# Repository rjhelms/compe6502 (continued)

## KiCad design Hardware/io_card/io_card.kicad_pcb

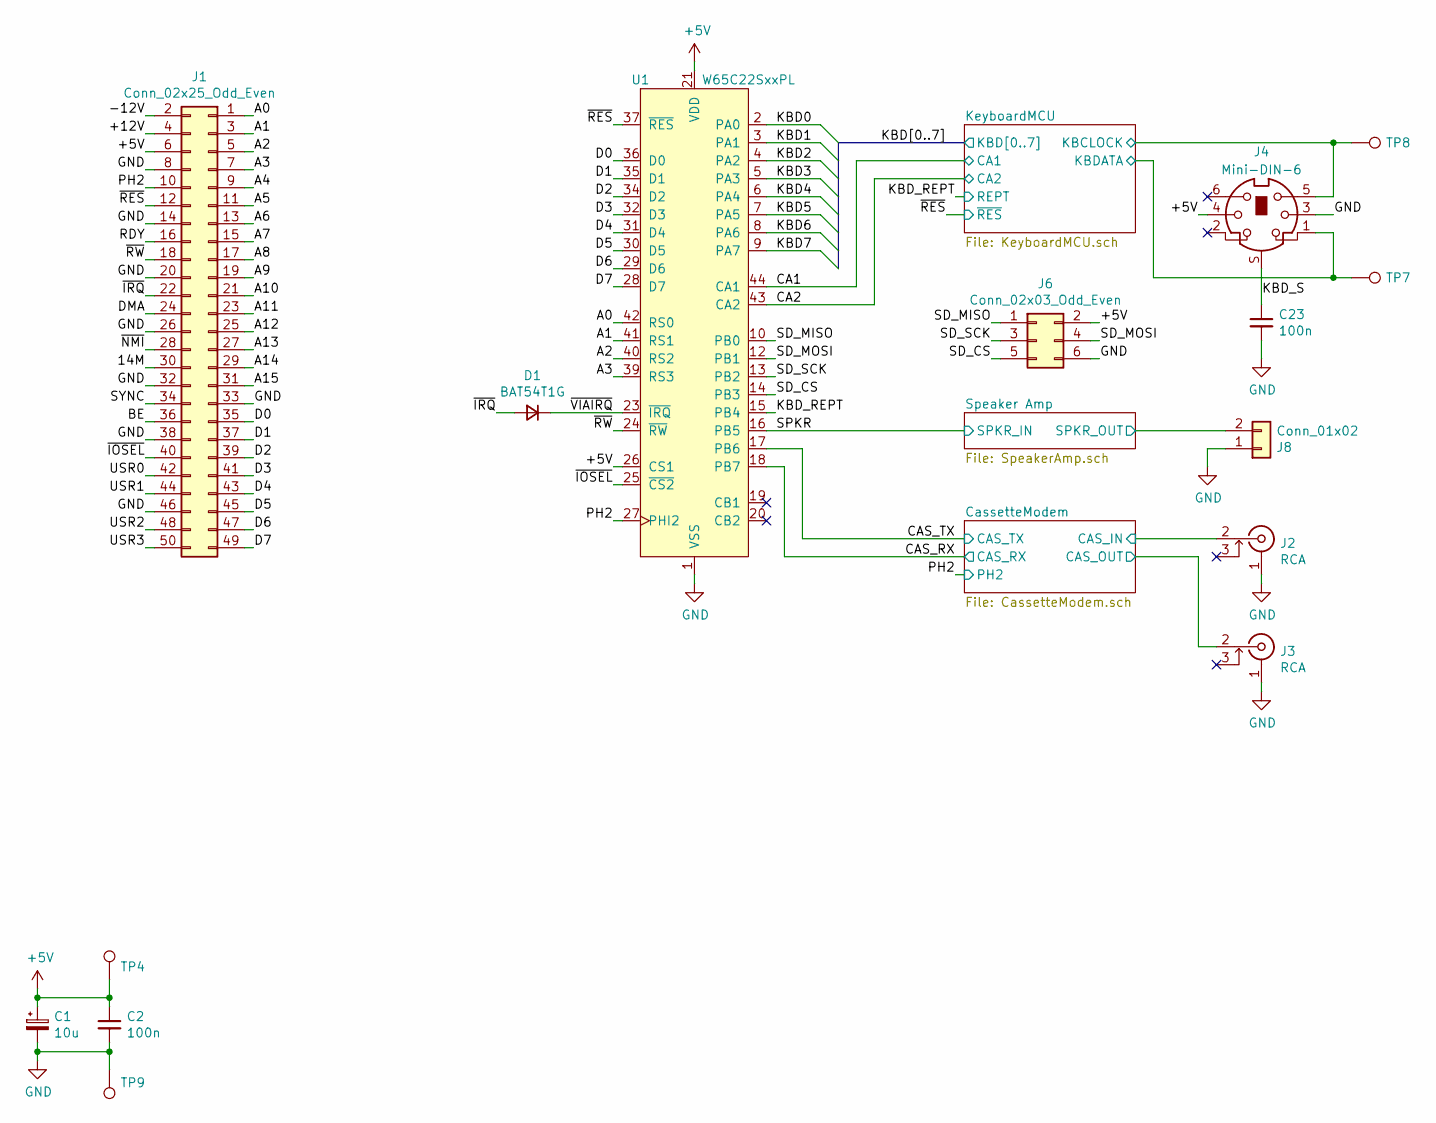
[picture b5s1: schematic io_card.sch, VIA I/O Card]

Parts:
C1: 10u; C_0805_2012Metric; MPN GRM21BR61E106KA73L
C2, C23: 100n; C_0805_2012Metric; MPN 08055C104JAT2A
D1: BAT54T1G; D_SOD-123; MPN BAT54T1G
J1: Conn_02x25_Odd_Even; EDAC_345-050-520-202_CardEdge; MPN 345-050-520-202
J2, J3: RCA; Jack_RCA_Switchcraft_PJRAN1X1UxxX; MPN PJRAN1X1U02AUX
J4: Mini-DIN-6; CUI_MD-60S; MPN MD-60S
J6: Conn_02x03_Odd_Even; IDC-Header_2x03_P2.54mm_Vertical; MPN 54020-44030LF
J8: Conn_01x02; PinHeader_1x02_P2.54mm_Horizontal
TP4, TP7, TP8, TP9: TestPoint; TestPoint_Keystone_5015_Micro-Minature; MPN S1751-46R
U1: W65C22SxxPL; PLCC-44_THT-Socket; MPN W65C22S6TPLG-14

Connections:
+5V: C1.1, C2.1, J1.6, J4.4, J6.2, TP4.1, U1.21 (VDD), U1.26 (CS1); also elsewhere on the board
/14M: J1.30
/+12V: J1.4
/-12V: J1.2
/A0: J1.1, U1.42 (RS0)
/A1: J1.3, U1.41 (RS1)
/A2: J1.5, U1.40 (RS2)
/A3: J1.7, U1.39 (RS3)
/A4: J1.9
/A5: J1.11
/A6: J1.13
/A7: J1.15
/A8: J1.17
/A9: J1.19
/A10: J1.21
/A11: J1.23
/A12: J1.25
/A13: J1.27
/A14: J1.29
/A15: J1.31
/BE: J1.36
/CA1: U1.44 (CA1); also elsewhere on the board
/CA2: U1.43 (CA2); also elsewhere on the board
/CAS_RX: U1.18 (PB7); also elsewhere on the board
/CAS_TX: U1.17 (PB6); also elsewhere on the board
/CassetteModem/CAS_IN: J2.2 (In); also elsewhere on the board
/CassetteModem/CAS_OUT: J3.2 (In); also elsewhere on the board
/D0: J1.35, U1.36 (D0)
/D1: J1.37, U1.35 (D1)
/D2: J1.39, U1.34 (D2)
/D3: J1.41, U1.32 (D3)
/D4: J1.43, U1.31 (D4)
/D5: J1.45, U1.30 (D5)
/D6: J1.47, U1.29 (D6)
/D7: J1.49, U1.28 (D7)
/DMA: J1.24
/KBD0: U1.2 (PA0); also elsewhere on the board
/KBD1: U1.3 (PA1); also elsewhere on the board
/KBD2: U1.4 (PA2); also elsewhere on the board
/KBD3: U1.5 (PA3); also elsewhere on the board
/KBD4: U1.6 (PA4); also elsewhere on the board
/KBD5: U1.7 (PA5); also elsewhere on the board
/KBD6: U1.8 (PA6); also elsewhere on the board
/KBD7: U1.9 (PA7); also elsewhere on the board
/KBD_REPT: U1.15 (PB4); also elsewhere on the board
/KBD_S: C23.1, J4.S
/KeyboardMCU/KBCLOCK: J4.5, TP8.1; also elsewhere on the board
/KeyboardMCU/KBDATA: J4.1, TP7.1; also elsewhere on the board
/PH2: J1.10, U1.27 (PHI2); also elsewhere on the board
/RDY: J1.16
/SD_CS: J6.5, U1.14 (PB3)
/SD_MISO: J6.1, U1.10 (PB0)
/SD_MOSI: J6.4, U1.12 (PB1)
/SD_SCK: J6.3, U1.13 (PB2)
/SPKR: U1.16 (PB5); also elsewhere on the board
/SYNC: J1.34
/Speaker Amp/SPKR_OUT: J8.2; also elsewhere on the board
/USR0: J1.42
/USR1: J1.44
/USR2: J1.48
/USR3: J1.50
/~IOSEL: J1.40, U1.25 (~CS2)
/~IRQ: D1.2 (A), J1.22
/~NMI: J1.28
/~RES: J1.12, U1.37 (~RES); also elsewhere on the board
/~RW: J1.18, U1.24 (~RW)
/~VIAIRQ: D1.1 (K), U1.23 (~IRQ)
GND: C1.2, C2.2, C23.2, J1.8, J1.14, J1.20, J1.26, J1.32, J1.33, J1.38, J1.46, J2.1 (Ext), J3.1 (Ext), J4.3, J6.6, J8.1, TP9.1, U1.1 (VSS); also elsewhere on the board

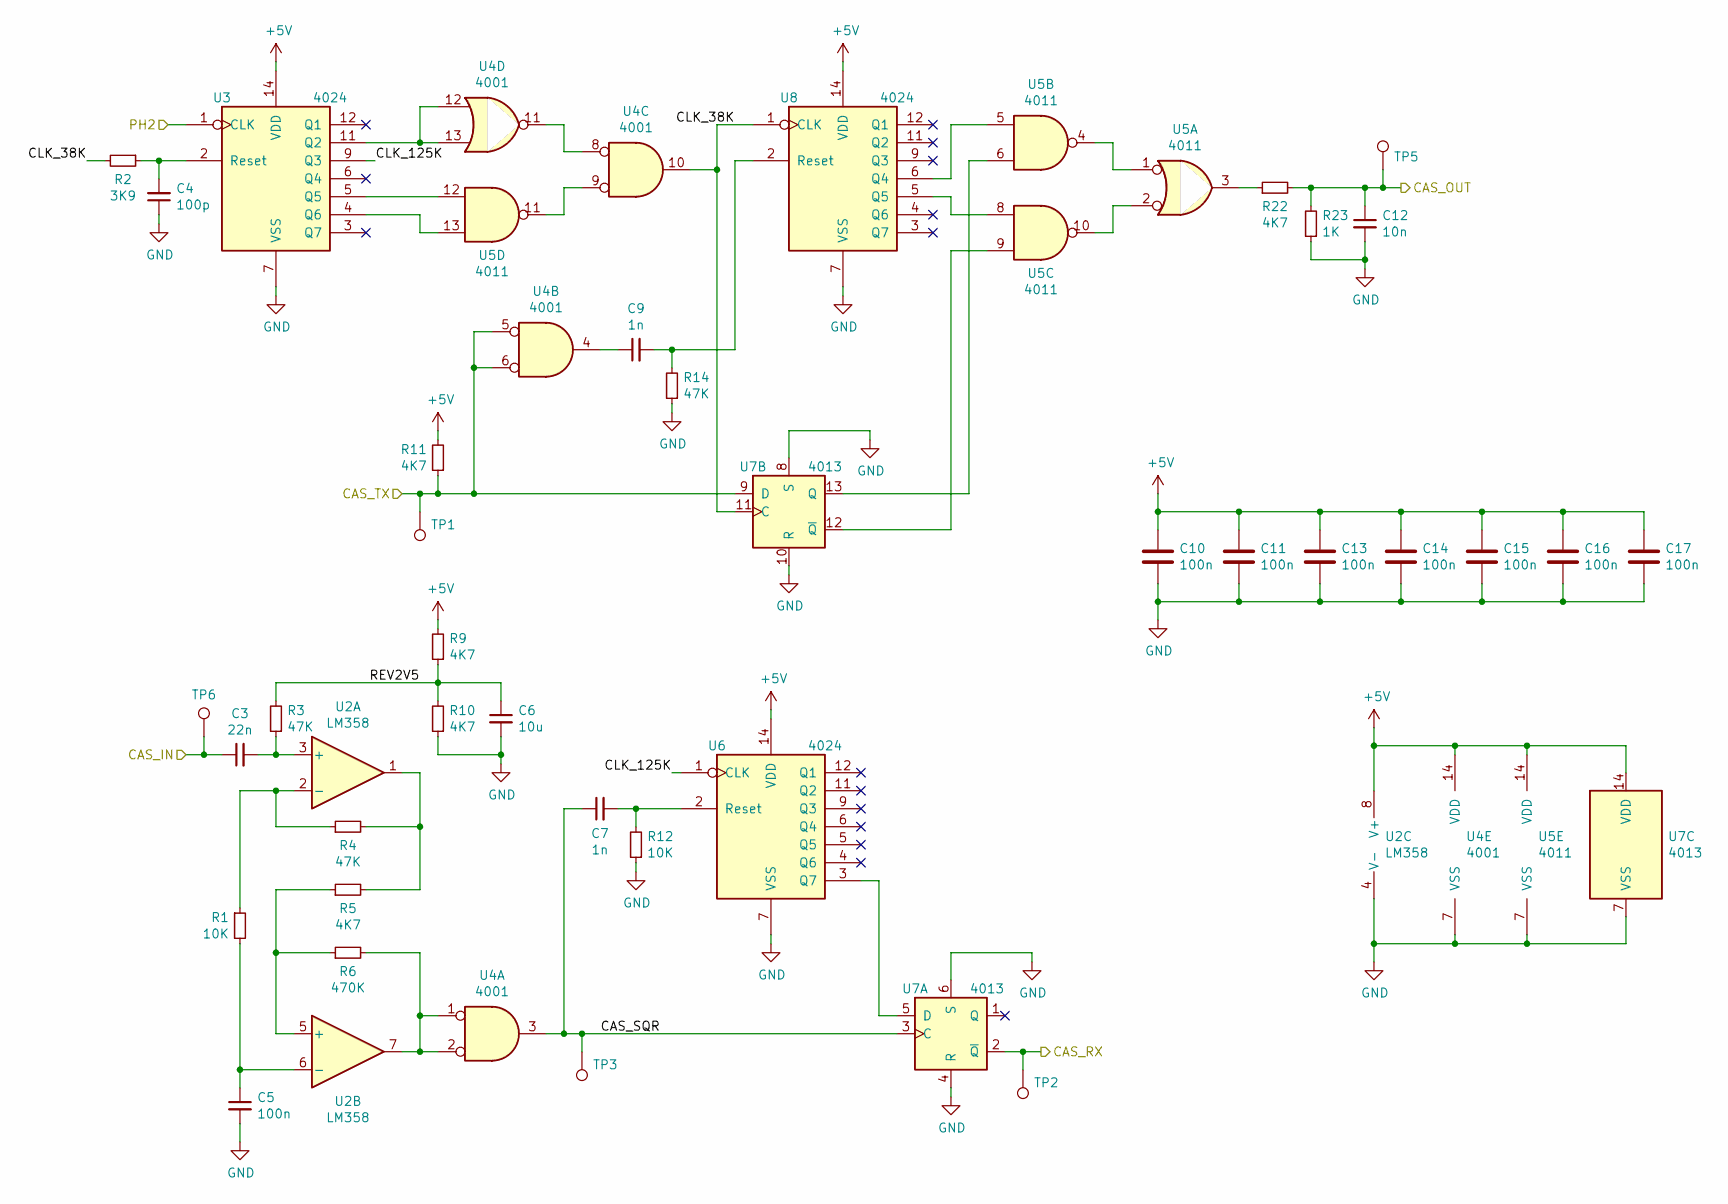
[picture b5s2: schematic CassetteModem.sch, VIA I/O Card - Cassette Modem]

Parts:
C3: 22n; C_0805_2012Metric; MPN CL21B223KBANNWC
C4: 100p; C_0805_2012Metric; MPN 885012007034
C5, C10, C11, C13, C14, C15, C16, C17: 100n; C_0805_2012Metric; MPN 08055C104JAT2A
C6: 10u; C_0805_2012Metric; MPN GRM21BR61E106KA73L
C7, C9: 1n; C_0805_2012Metric; MPN CL21B102KBANNND
C12: 10n; C_0805_2012Metric; MPN CL21B103KBANFNC
R1, R12: 10K; R_0805_2012Metric; MPN MCSR08X1002FTL
R2: 3K9; R_0805_2012Metric; MPN CR0805-FX-3901ELF
R3, R4, R14: 47K; R_0805_2012Metric; MPN RC0805FR-0747KL
R5, R9, R10, R11, R22: 4K7; R_0805_2012Metric; MPN CRCW08054K70FKTA
R6: 470K; R_0805_2012Metric; MPN RC0805FR-07470KL
R23: 1K; R_0805_2012Metric; MPN CRCW08051K00FKEB
TP1, TP2, TP3, TP5, TP6: TestPoint; TestPoint_Keystone_5015_Micro-Minature; MPN S1751-46R
U2: LM358; SOIC-8_3.9x4.9mm_P1.27mm; MPN LM358PSR
U3, U6, U8: 4024; SOIC-14_3.9x8.7mm_P1.27mm; MPN CD4024BM96
U4: 4001; SOIC-14_3.9x8.7mm_P1.27mm; MPN HEF4001BT-Q100J
U5: 4011; SOIC-14_3.9x8.7mm_P1.27mm; MPN MC14011BDR2G
U7: 4013; SOIC-14_3.9x8.7mm_P1.27mm; MPN HEF4013BT,653

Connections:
+5V: C10.1, C11.1, C13.1, C14.1, C15.1, C16.1, C17.1, R9.2, R11.2, U2.8 (V+), U3.14 (VDD), U4.14 (VDD), U5.14 (VDD), U6.14 (VDD), U7.14 (VDD), U8.14 (VDD); also elsewhere on the board
/CAS_RX: TP2.1, U7.2 (~Q); also elsewhere on the board
/CAS_TX: R11.1, TP1.1, U4.5, U4.6, U7.9 (D); also elsewhere on the board
/CassetteModem/CAS_IN: C3.1, TP6.1; also elsewhere on the board
/CassetteModem/CAS_OUT: C12.1, R22.2, R23.2, TP5.1; also elsewhere on the board
/CassetteModem/CAS_SQR: C7.1, TP3.1, U4.3, U7.3 (C)
/CassetteModem/CLK_38K: R2.2, U4.10, U7.11 (C), U8.1 (CLK)
/CassetteModem/CLK_125K: U3.9 (Q3), U6.1 (CLK)
/CassetteModem/REV2V5: C6.1, R3.2, R9.1, R10.2
/PH2: U3.1 (CLK); also elsewhere on the board
GND: C4.1, C5.2, C6.2, C10.2, C11.2, C12.2, C13.2, C14.2, C15.2, C16.2, C17.2, R10.1, R12.1, R14.1, R23.1, U2.4 (V-), U3.7 (VSS), U4.7 (VSS), U5.7 (VSS), U6.7 (VSS), U7.4 (R), U7.6 (S), U7.7 (VSS), U7.8 (S), U7.10 (R), U8.7 (VSS); also elsewhere on the board
unnamed: C3.2, R3.1, U2.3 (+)
unnamed: C4.2, R2.1, U3.2 (Reset)
unnamed: C5.1, R1.2, U2.6 (-)
unnamed: C7.2, R12.2, U6.2 (Reset)
unnamed: C9.1, U4.4
unnamed: C9.2, R14.2, U8.2 (Reset)
unnamed: R1.1, R4.1, U2.2 (-)
unnamed: R4.2, R5.2, U2.1
unnamed: R5.1, R6.1, U2.5 (+)
unnamed: R6.2, U2.7, U4.1, U4.2
unnamed: R22.1, U5.3
unnamed: U3.4 (Q6), U5.13
unnamed: U3.5 (Q5), U5.12
unnamed: U3.11 (Q2), U4.12, U4.13
unnamed: U4.9, U5.11
unnamed: U4.8, U4.11
unnamed: U5.1, U5.4
unnamed: U5.5, U8.6 (Q4)
unnamed: U5.6, U7.13 (Q)
unnamed: U5.8, U8.5 (Q5)
unnamed: U5.9, U7.12 (~Q)
unnamed: U5.2, U5.10
unnamed: U6.3 (Q7), U7.5 (D)

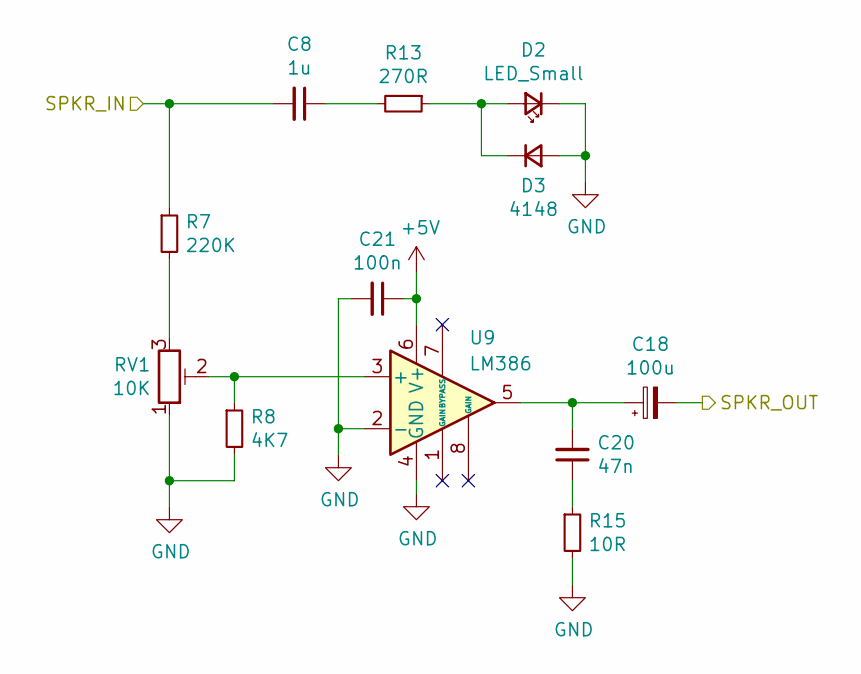
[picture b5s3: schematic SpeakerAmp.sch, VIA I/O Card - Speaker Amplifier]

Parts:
C8: 1u; C_0805_2012Metric; MPN 08053C105K4Z4A
C18: 100u; CP_Elec_6.3x5.4; MPN 865080343009
C20: 47n; C_0805_2012Metric; MPN CL21B473KBCNNNC
C21: 100n; C_0805_2012Metric; MPN 08055C104JAT2A
D2: LED_Small; LED_0805_2012Metric; MPN 598-8170-107F
D3: 4148; D_SOD-123; MPN MMSD4148T1G
R7: 220K; R_0805_2012Metric; MPN RC0805FR-07220KL
R8: 4K7; R_0805_2012Metric; MPN CRCW08054K70FKTA
R13: 270R; R_0805_2012Metric; MPN RC0805FR-07270RL
R15: 10R; R_0805_2012Metric; MPN CR0805-FX-10R0ELF
RV1: 10K; Potentiometer_Copal_CT-6EP; MPN CT6EP103
U9: LM386; SOIC-8_3.9x4.9mm_P1.27mm; MPN LM386M-1/NOPB

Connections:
+5V: C21.1, U9.6 (V+); also elsewhere on the board
/SPKR: C8.2, R7.1; also elsewhere on the board
/Speaker Amp/SPKR_OUT: C18.2; also elsewhere on the board
GND: C21.2, D2.1 (K), D3.2 (A), R8.2, R15.2, RV1.1, U9.2 (-), U9.4 (GND); also elsewhere on the board
unnamed: C8.1, R13.2
unnamed: C18.1, C20.2, U9.5
unnamed: C20.1, R15.1
unnamed: D2.2 (A), D3.1 (K), R13.1
unnamed: R7.2, RV1.3
unnamed: R8.1, RV1.2, U9.3 (+)

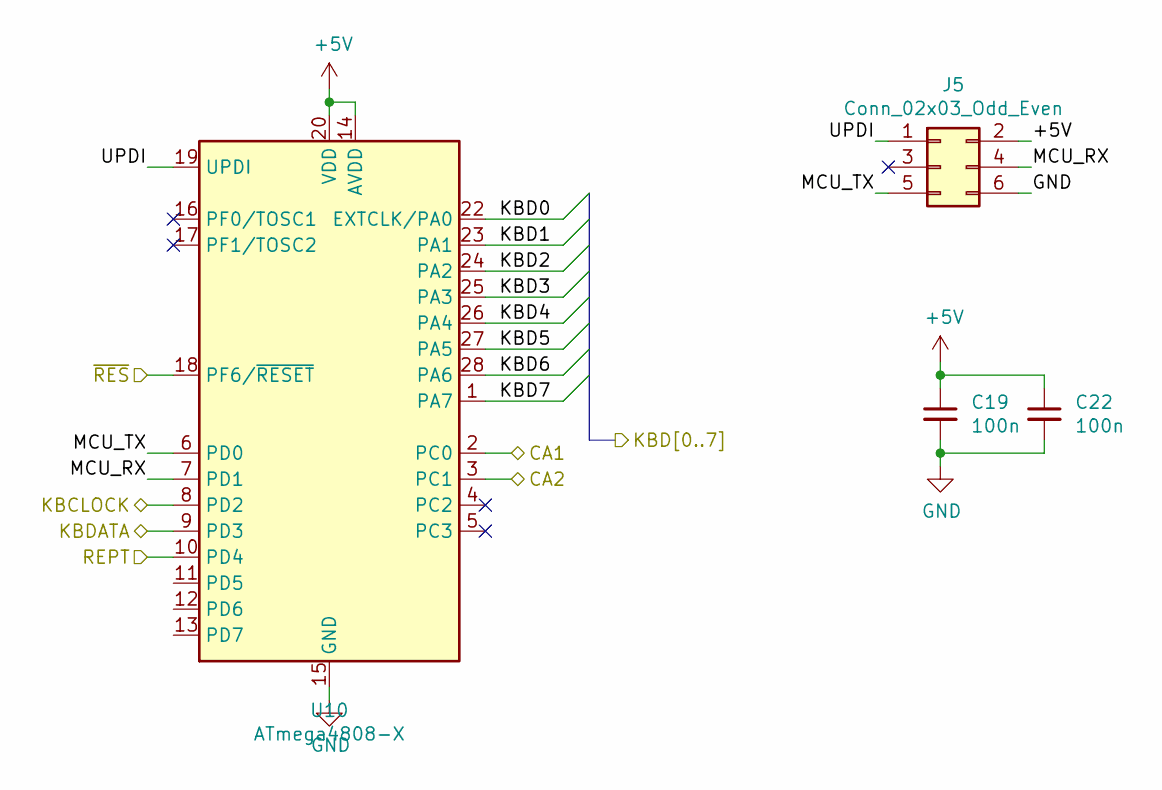
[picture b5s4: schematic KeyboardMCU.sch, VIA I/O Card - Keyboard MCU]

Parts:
C19, C22: 100n; C_0805_2012Metric; MPN 08055C104JAT2A
J5: Conn_02x03_Odd_Even; IDC-Header_2x03_P2.54mm_Vertical; MPN 54020-44030LF
U10: ATmega4808-X; SSOP-28_5.3x10.2mm_P0.65mm; MPN ATMEGA4808-XUR

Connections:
+5V: C19.1, C22.1, J5.2, U10.14 (AVDD), U10.20 (VDD); also elsewhere on the board
/CA1: U10.2 (PC0); also elsewhere on the board
/CA2: U10.3 (PC1); also elsewhere on the board
/KBD0: U10.22 (EXTCLK/PA0); also elsewhere on the board
/KBD1: U10.23 (PA1); also elsewhere on the board
/KBD2: U10.24 (PA2); also elsewhere on the board
/KBD3: U10.25 (PA3); also elsewhere on the board
/KBD4: U10.26 (PA4); also elsewhere on the board
/KBD5: U10.27 (PA5); also elsewhere on the board
/KBD6: U10.28 (PA6); also elsewhere on the board
/KBD7: U10.1 (PA7); also elsewhere on the board
/KBD_REPT: U10.10 (PD4); also elsewhere on the board
/KeyboardMCU/KBCLOCK: U10.8 (PD2); also elsewhere on the board
/KeyboardMCU/KBDATA: U10.9 (PD3); also elsewhere on the board
/KeyboardMCU/MCU_RX: J5.4, U10.7 (PD1)
/KeyboardMCU/MCU_TX: J5.5, U10.6 (PD0)
/KeyboardMCU/UPDI: J5.1, U10.19 (UPDI)
/~RES: U10.18 (PF6/~RESET); also elsewhere on the board
GND: C19.2, C22.2, J5.6, U10.15 (GND), U10.21 (GND); also elsewhere on the board

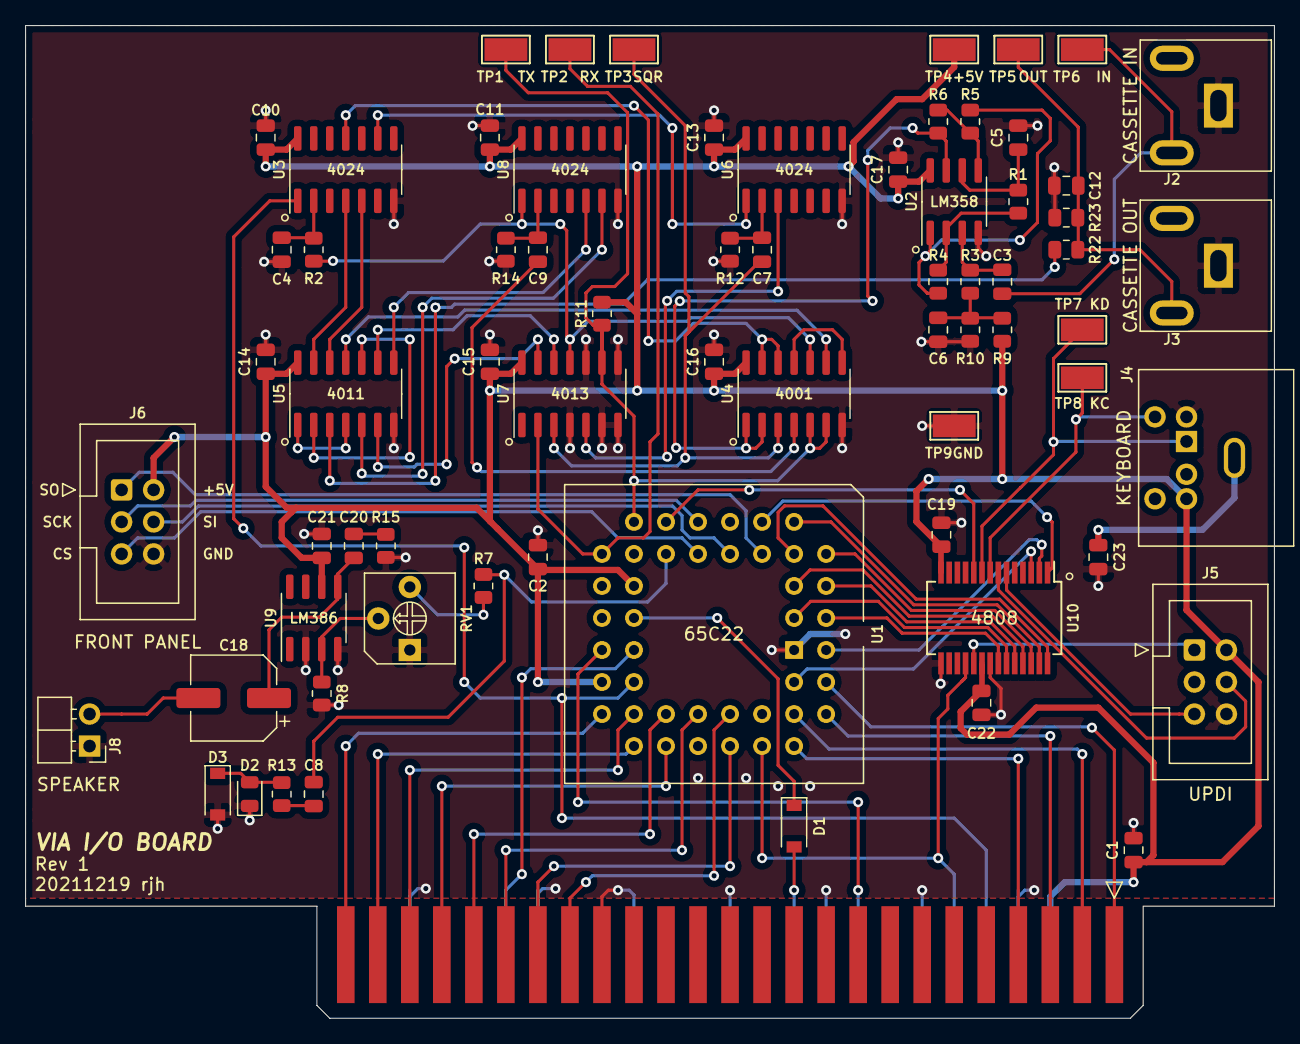
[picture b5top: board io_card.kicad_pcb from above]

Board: 2 copper layers, 99.1 x 78.7 mm, 70 parts (0 on the bottom side), 80 nets.

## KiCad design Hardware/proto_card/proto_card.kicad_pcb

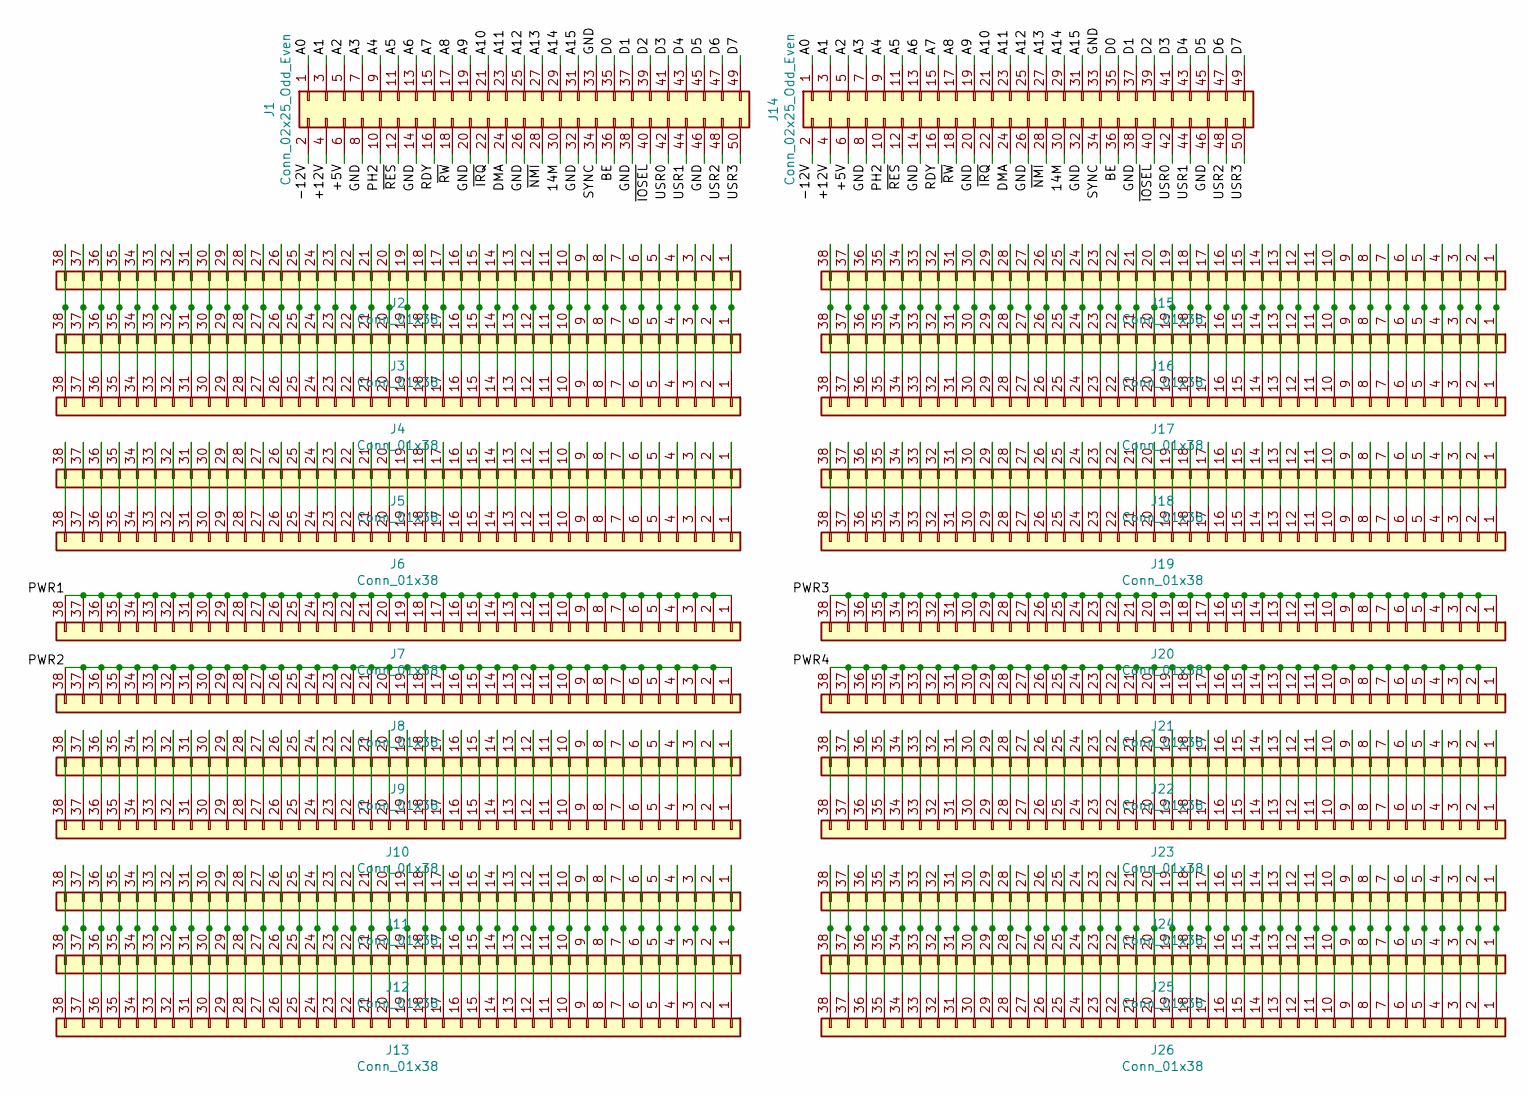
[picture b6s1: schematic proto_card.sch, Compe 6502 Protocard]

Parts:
J1: Conn_02x25_Odd_Even; EDAC_345-050-520-202_CardEdge; MPN 345-050-520-202
J2, J3, J4, J5, J6, J7, J8, J9, J10, J11, J12, J13, J15, J16, J17, J18, J19, J20, J21, J22, J23, J24, J25, J26: Conn_01x38; BreadboardRow_1x38_P2.54
J14: Conn_02x25_Odd_Even; PinHeader_2x25_P2.54mm_Vertical; MPN 345-050-520-202

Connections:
/14M: J1.30, J14.30
/+5V: J1.6, J14.6
/+12V: J1.4, J14.4
/-12V: J1.2, J14.2
/A0: J1.1, J14.1
/A1: J1.3, J14.3
/A2: J1.5, J14.5
/A3: J1.7, J14.7
/A4: J1.9, J14.9
/A5: J1.11, J14.11
/A6: J1.13, J14.13
/A7: J1.15, J14.15
/A8: J1.17, J14.17
/A9: J1.19, J14.19
/A10: J1.21, J14.21
/A11: J1.23, J14.23
/A12: J1.25, J14.25
/A13: J1.27, J14.27
/A14: J1.29, J14.29
/A15: J1.31, J14.31
/BE: J1.36, J14.36
/D0: J1.35, J14.35
/D1: J1.37, J14.37
/D2: J1.39, J14.39
/D3: J1.41, J14.41
/D4: J1.43, J14.43
/D5: J1.45, J14.45
/D6: J1.47, J14.47
/D7: J1.49, J14.49
/DMA: J1.24, J14.24
/GND: J1.8, J1.14, J1.20, J1.26, J1.32, J1.33, J1.38, J1.46, J14.8, J14.14, J14.20, J14.26, J14.32, J14.33, J14.38, J14.46
/PH2: J1.10, J14.10
/PWR1: J7.1, J7.2, J7.3, J7.4, J7.5, J7.6, J7.7, J7.8, J7.9, J7.10, J7.11, J7.12, J7.13, J7.14, J7.15, J7.16, J7.17, J7.18, J7.19, J7.20, J7.21, J7.22, J7.23, J7.24, J7.25, J7.26, J7.27, J7.28, J7.29, J7.30, J7.31, J7.32, J7.33, J7.34, J7.35, J7.36, J7.37, J7.38
/PWR2: J8.1, J8.2, J8.3, J8.4, J8.5, J8.6, J8.7, J8.8, J8.9, J8.10, J8.11, J8.12, J8.13, J8.14, J8.15, J8.16, J8.17, J8.18, J8.19, J8.20, J8.21, J8.22, J8.23, J8.24, J8.25, J8.26, J8.27, J8.28, J8.29, J8.30, J8.31, J8.32, J8.33, J8.34, J8.35, J8.36, J8.37, J8.38
/PWR3: J20.1, J20.2, J20.3, J20.4, J20.5, J20.6, J20.7, J20.8, J20.9, J20.10, J20.11, J20.12, J20.13, J20.14, J20.15, J20.16, J20.17, J20.18, J20.19, J20.20, J20.21, J20.22, J20.23, J20.24, J20.25, J20.26, J20.27, J20.28, J20.29, J20.30, J20.31, J20.32, J20.33, J20.34, J20.35, J20.36, J20.37, J20.38
/PWR4: J21.1, J21.2, J21.3, J21.4, J21.5, J21.6, J21.7, J21.8, J21.9, J21.10, J21.11, J21.12, J21.13, J21.14, J21.15, J21.16, J21.17, J21.18, J21.19, J21.20, J21.21, J21.22, J21.23, J21.24, J21.25, J21.26, J21.27, J21.28, J21.29, J21.30, J21.31, J21.32, J21.33, J21.34, J21.35, J21.36, J21.37, J21.38
/RDY: J1.16, J14.16
/SYNC: J1.34, J14.34
/USR0: J1.42, J14.42
/USR1: J1.44, J14.44
/USR2: J1.48, J14.48
/USR3: J1.50, J14.50
/~IOSEL: J1.40, J14.40
/~IRQ: J1.22, J14.22
/~NMI: J1.28, J14.28
/~RES: J1.12, J14.12
/~RW: J1.18, J14.18
unnamed: J2.1, J3.1, J4.1
unnamed: J2.2, J3.2, J4.2
unnamed: J2.3, J3.3, J4.3
unnamed: J2.4, J3.4, J4.4
unnamed: J2.5, J3.5, J4.5
unnamed: J2.6, J3.6, J4.6
unnamed: J2.7, J3.7, J4.7
unnamed: J2.8, J3.8, J4.8
unnamed: J2.9, J3.9, J4.9
unnamed: J2.10, J3.10, J4.10
unnamed: J2.11, J3.11, J4.11
unnamed: J2.12, J3.12, J4.12
unnamed: J2.13, J3.13, J4.13
unnamed: J2.14, J3.14, J4.14
unnamed: J2.15, J3.15, J4.15
unnamed: J2.16, J3.16, J4.16
unnamed: J2.17, J3.17, J4.17
unnamed: J2.18, J3.18, J4.18
unnamed: J2.19, J3.19, J4.19
unnamed: J2.20, J3.20, J4.20
unnamed: J2.21, J3.21, J4.21
unnamed: J2.22, J3.22, J4.22
unnamed: J2.23, J3.23, J4.23
unnamed: J2.24, J3.24, J4.24
unnamed: J2.25, J3.25, J4.25
unnamed: J2.26, J3.26, J4.26
unnamed: J2.27, J3.27, J4.27
unnamed: J2.28, J3.28, J4.28
unnamed: J2.29, J3.29, J4.29
unnamed: J2.30, J3.30, J4.30
unnamed: J2.31, J3.31, J4.31
unnamed: J2.32, J3.32, J4.32
unnamed: J2.33, J3.33, J4.33
unnamed: J2.34, J3.34, J4.34
unnamed: J2.35, J3.35, J4.35
unnamed: J2.36, J3.36, J4.36
unnamed: J2.37, J3.37, J4.37
unnamed: J2.38, J3.38, J4.38
unnamed: J5.1, J6.1
unnamed: J5.2, J6.2
unnamed: J5.3, J6.3
unnamed: J5.4, J6.4
unnamed: J5.5, J6.5
unnamed: J5.6, J6.6
unnamed: J5.7, J6.7
unnamed: J5.8, J6.8
unnamed: J5.9, J6.9
unnamed: J5.10, J6.10
unnamed: J5.11, J6.11
unnamed: J5.12, J6.12
unnamed: J5.13, J6.13
unnamed: J5.14, J6.14
unnamed: J5.15, J6.15
unnamed: J5.16, J6.16
unnamed: J5.17, J6.17
unnamed: J5.18, J6.18
unnamed: J5.19, J6.19
unnamed: J5.20, J6.20
unnamed: J5.21, J6.21
unnamed: J5.22, J6.22
unnamed: J5.23, J6.23
unnamed: J5.24, J6.24
unnamed: J5.25, J6.25
unnamed: J5.26, J6.26
unnamed: J5.27, J6.27
unnamed: J5.28, J6.28
unnamed: J5.29, J6.29
unnamed: J5.30, J6.30
unnamed: J5.31, J6.31
unnamed: J5.32, J6.32
unnamed: J5.33, J6.33
unnamed: J5.34, J6.34
unnamed: J5.35, J6.35
unnamed: J5.36, J6.36
unnamed: J5.37, J6.37
unnamed: J5.38, J6.38
unnamed: J9.1, J10.1
unnamed: J9.2, J10.2
unnamed: J9.3, J10.3
unnamed: J9.4, J10.4
unnamed: J9.5, J10.5
unnamed: J9.6, J10.6
unnamed: J9.7, J10.7
unnamed: J9.8, J10.8
unnamed: J9.9, J10.9
unnamed: J9.10, J10.10
unnamed: J9.11, J10.11
unnamed: J9.12, J10.12
unnamed: J9.13, J10.13
unnamed: J9.14, J10.14
unnamed: J9.15, J10.15
unnamed: J9.16, J10.16
unnamed: J9.17, J10.17
unnamed: J9.18, J10.18
unnamed: J9.19, J10.19
unnamed: J9.20, J10.20
unnamed: J9.21, J10.21
unnamed: J9.22, J10.22
unnamed: J9.23, J10.23
unnamed: J9.24, J10.24
unnamed: J9.25, J10.25
unnamed: J9.26, J10.26
unnamed: J9.27, J10.27
unnamed: J9.28, J10.28
unnamed: J9.29, J10.29
unnamed: J9.30, J10.30
unnamed: J9.31, J10.31
unnamed: J9.32, J10.32
unnamed: J9.33, J10.33
unnamed: J9.34, J10.34
unnamed: J9.35, J10.35
unnamed: J9.36, J10.36
unnamed: J9.37, J10.37
unnamed: J9.38, J10.38
unnamed: J11.1, J12.1, J13.1
unnamed: J11.2, J12.2, J13.2
unnamed: J11.3, J12.3, J13.3
unnamed: J11.4, J12.4, J13.4
unnamed: J11.5, J12.5, J13.5
unnamed: J11.6, J12.6, J13.6
unnamed: J11.7, J12.7, J13.7
unnamed: J11.8, J12.8, J13.8
unnamed: J11.9, J12.9, J13.9
unnamed: J11.10, J12.10, J13.10
unnamed: J11.11, J12.11, J13.11
unnamed: J11.12, J12.12, J13.12
unnamed: J11.13, J12.13, J13.13
unnamed: J11.14, J12.14, J13.14
unnamed: J11.15, J12.15, J13.15
unnamed: J11.16, J12.16, J13.16
unnamed: J11.17, J12.17, J13.17
unnamed: J11.18, J12.18, J13.18
unnamed: J11.19, J12.19, J13.19
unnamed: J11.20, J12.20, J13.20
unnamed: J11.21, J12.21, J13.21
unnamed: J11.22, J12.22, J13.22
unnamed: J11.23, J12.23, J13.23
unnamed: J11.24, J12.24, J13.24
unnamed: J11.25, J12.25, J13.25
unnamed: J11.26, J12.26, J13.26
unnamed: J11.27, J12.27, J13.27
unnamed: J11.28, J12.28, J13.28
unnamed: J11.29, J12.29, J13.29
unnamed: J11.30, J12.30, J13.30
unnamed: J11.31, J12.31, J13.31
unnamed: J11.32, J12.32, J13.32
unnamed: J11.33, J12.33, J13.33
unnamed: J11.34, J12.34, J13.34
unnamed: J11.35, J12.35, J13.35
unnamed: J11.36, J12.36, J13.36
unnamed: J11.37, J12.37, J13.37
unnamed: J11.38, J12.38, J13.38
unnamed: J15.1, J16.1, J17.1
unnamed: J15.2, J16.2, J17.2
unnamed: J15.3, J16.3, J17.3
unnamed: J15.4, J16.4, J17.4
unnamed: J15.5, J16.5, J17.5
unnamed: J15.6, J16.6, J17.6
unnamed: J15.7, J16.7, J17.7
unnamed: J15.8, J16.8, J17.8
unnamed: J15.9, J16.9, J17.9
unnamed: J15.10, J16.10, J17.10
unnamed: J15.11, J16.11, J17.11
unnamed: J15.12, J16.12, J17.12
unnamed: J15.13, J16.13, J17.13
unnamed: J15.14, J16.14, J17.14
unnamed: J15.15, J16.15, J17.15
unnamed: J15.16, J16.16, J17.16
unnamed: J15.17, J16.17, J17.17
unnamed: J15.18, J16.18, J17.18
unnamed: J15.19, J16.19, J17.19
unnamed: J15.20, J16.20, J17.20
unnamed: J15.21, J16.21, J17.21
unnamed: J15.22, J16.22, J17.22
unnamed: J15.23, J16.23, J17.23
unnamed: J15.24, J16.24, J17.24
unnamed: J15.25, J16.25, J17.25
unnamed: J15.26, J16.26, J17.26
unnamed: J15.27, J16.27, J17.27
unnamed: J15.28, J16.28, J17.28
unnamed: J15.29, J16.29, J17.29
unnamed: J15.30, J16.30, J17.30
unnamed: J15.31, J16.31, J17.31
unnamed: J15.32, J16.32, J17.32
unnamed: J15.33, J16.33, J17.33
unnamed: J15.34, J16.34, J17.34
unnamed: J15.35, J16.35, J17.35
unnamed: J15.36, J16.36, J17.36
unnamed: J15.37, J16.37, J17.37
unnamed: J15.38, J16.38, J17.38
unnamed: J18.1, J19.1
unnamed: J18.2, J19.2
unnamed: J18.3, J19.3
unnamed: J18.4, J19.4
unnamed: J18.5, J19.5
unnamed: J18.6, J19.6
unnamed: J18.7, J19.7
unnamed: J18.8, J19.8
unnamed: J18.9, J19.9
unnamed: J18.10, J19.10
unnamed: J18.11, J19.11
unnamed: J18.12, J19.12
unnamed: J18.13, J19.13
unnamed: J18.14, J19.14
unnamed: J18.15, J19.15
unnamed: J18.16, J19.16
unnamed: J18.17, J19.17
unnamed: J18.18, J19.18
unnamed: J18.19, J19.19
unnamed: J18.20, J19.20
unnamed: J18.21, J19.21
unnamed: J18.22, J19.22
unnamed: J18.23, J19.23
unnamed: J18.24, J19.24
unnamed: J18.25, J19.25
unnamed: J18.26, J19.26
unnamed: J18.27, J19.27
unnamed: J18.28, J19.28
unnamed: J18.29, J19.29
unnamed: J18.30, J19.30
unnamed: J18.31, J19.31
unnamed: J18.32, J19.32
unnamed: J18.33, J19.33
unnamed: J18.34, J19.34
unnamed: J18.35, J19.35
unnamed: J18.36, J19.36
unnamed: J18.37, J19.37
unnamed: J18.38, J19.38
unnamed: J22.1, J23.1
unnamed: J22.2, J23.2
unnamed: J22.3, J23.3
unnamed: J22.4, J23.4
unnamed: J22.5, J23.5
unnamed: J22.6, J23.6
unnamed: J22.7, J23.7
unnamed: J22.8, J23.8
unnamed: J22.9, J23.9
unnamed: J22.10, J23.10
unnamed: J22.11, J23.11
unnamed: J22.12, J23.12
unnamed: J22.13, J23.13
unnamed: J22.14, J23.14
unnamed: J22.15, J23.15
unnamed: J22.16, J23.16
unnamed: J22.17, J23.17
unnamed: J22.18, J23.18
unnamed: J22.19, J23.19
unnamed: J22.20, J23.20
unnamed: J22.21, J23.21
unnamed: J22.22, J23.22
unnamed: J22.23, J23.23
unnamed: J22.24, J23.24
unnamed: J22.25, J23.25
unnamed: J22.26, J23.26
unnamed: J22.27, J23.27
unnamed: J22.28, J23.28
unnamed: J22.29, J23.29
unnamed: J22.30, J23.30
unnamed: J22.31, J23.31
unnamed: J22.32, J23.32
unnamed: J22.33, J23.33
unnamed: J22.34, J23.34
unnamed: J22.35, J23.35
unnamed: J22.36, J23.36
unnamed: J22.37, J23.37
unnamed: J22.38, J23.38
unnamed: J24.1, J25.1, J26.1
unnamed: J24.2, J25.2, J26.2
unnamed: J24.3, J25.3, J26.3
unnamed: J24.4, J25.4, J26.4
unnamed: J24.5, J25.5, J26.5
unnamed: J24.6, J25.6, J26.6
unnamed: J24.7, J25.7, J26.7
unnamed: J24.8, J25.8, J26.8
unnamed: J24.9, J25.9, J26.9
unnamed: J24.10, J25.10, J26.10
unnamed: J24.11, J25.11, J26.11
unnamed: J24.12, J25.12, J26.12
unnamed: J24.13, J25.13, J26.13
unnamed: J24.14, J25.14, J26.14
unnamed: J24.15, J25.15, J26.15
unnamed: J24.16, J25.16, J26.16
unnamed: J24.17, J25.17, J26.17
unnamed: J24.18, J25.18, J26.18
unnamed: J24.19, J25.19, J26.19
unnamed: J24.20, J25.20, J26.20
unnamed: J24.21, J25.21, J26.21
unnamed: J24.22, J25.22, J26.22
unnamed: J24.23, J25.23, J26.23
unnamed: J24.24, J25.24, J26.24
unnamed: J24.25, J25.25, J26.25
unnamed: J24.26, J25.26, J26.26
unnamed: J24.27, J25.27, J26.27
unnamed: J24.28, J25.28, J26.28
unnamed: J24.29, J25.29, J26.29
unnamed: J24.30, J25.30, J26.30
unnamed: J24.31, J25.31, J26.31
unnamed: J24.32, J25.32, J26.32
unnamed: J24.33, J25.33, J26.33
unnamed: J24.34, J25.34, J26.34
unnamed: J24.35, J25.35, J26.35
unnamed: J24.36, J25.36, J26.36
unnamed: J24.37, J25.37, J26.37
unnamed: J24.38, J25.38, J26.38

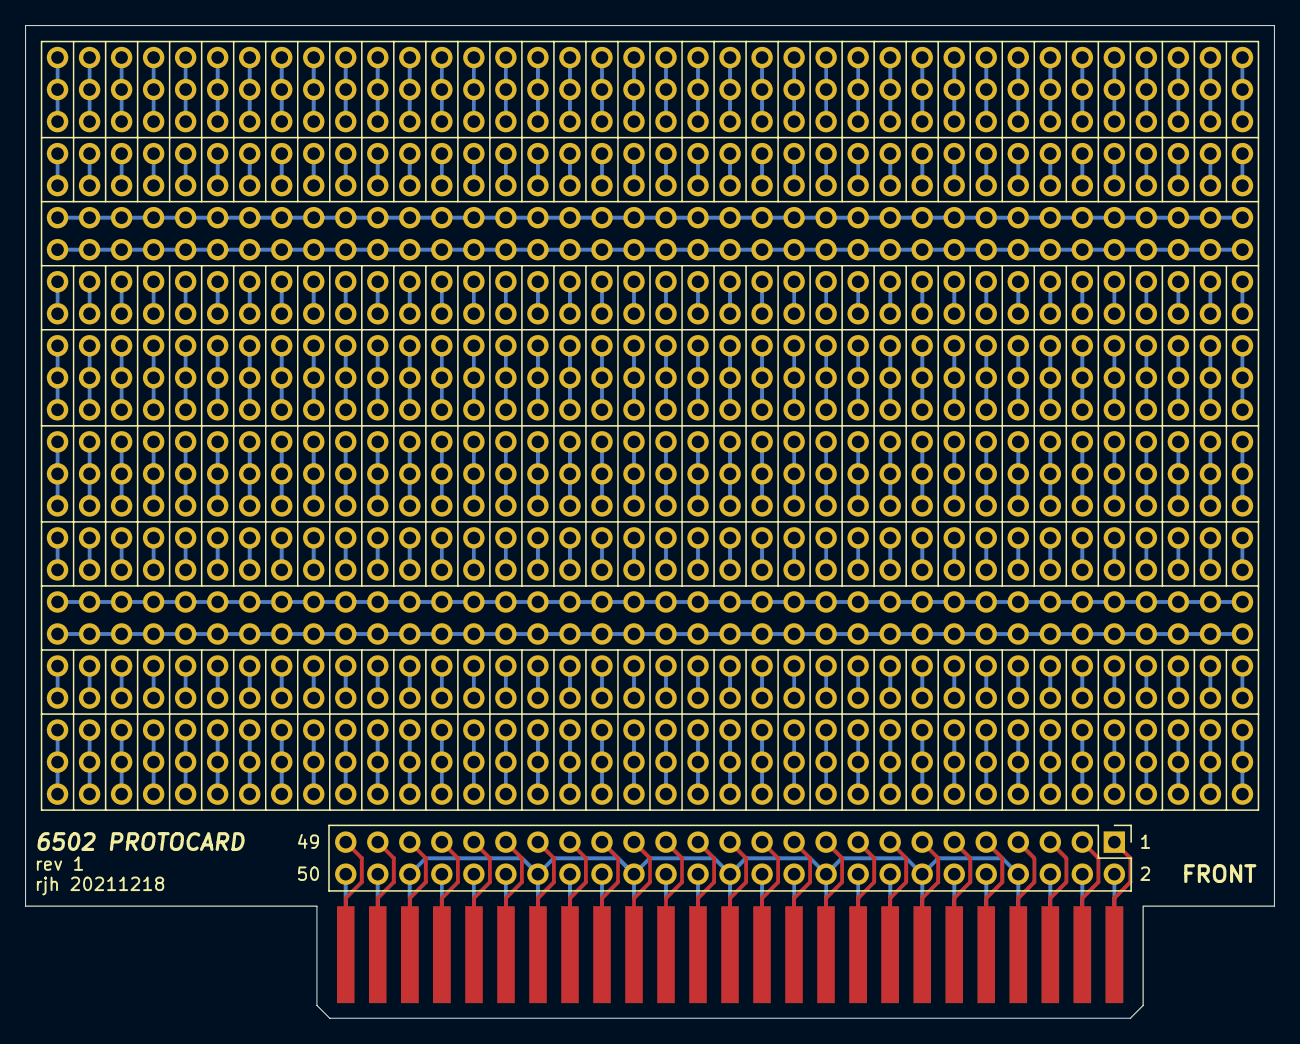
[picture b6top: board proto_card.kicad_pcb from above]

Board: 2 copper layers, 99.1 x 78.7 mm, 26 parts (0 on the bottom side), 351 nets.
